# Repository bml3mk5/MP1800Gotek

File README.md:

# ディスクインターフェース for MP-1800 / MP-1805 on 日立ベーシックマスターレベル３

## フォルダ構成

    Board/ ......................... 基板設計(KiCAD Version 6)

-----
# Disk Interface for MP-1800 / MP-1805 on HITACH BASIC MASTER LEVEL3

## Folders:

    Board/ ......................... Circuit board design(KiCAD Version 6)

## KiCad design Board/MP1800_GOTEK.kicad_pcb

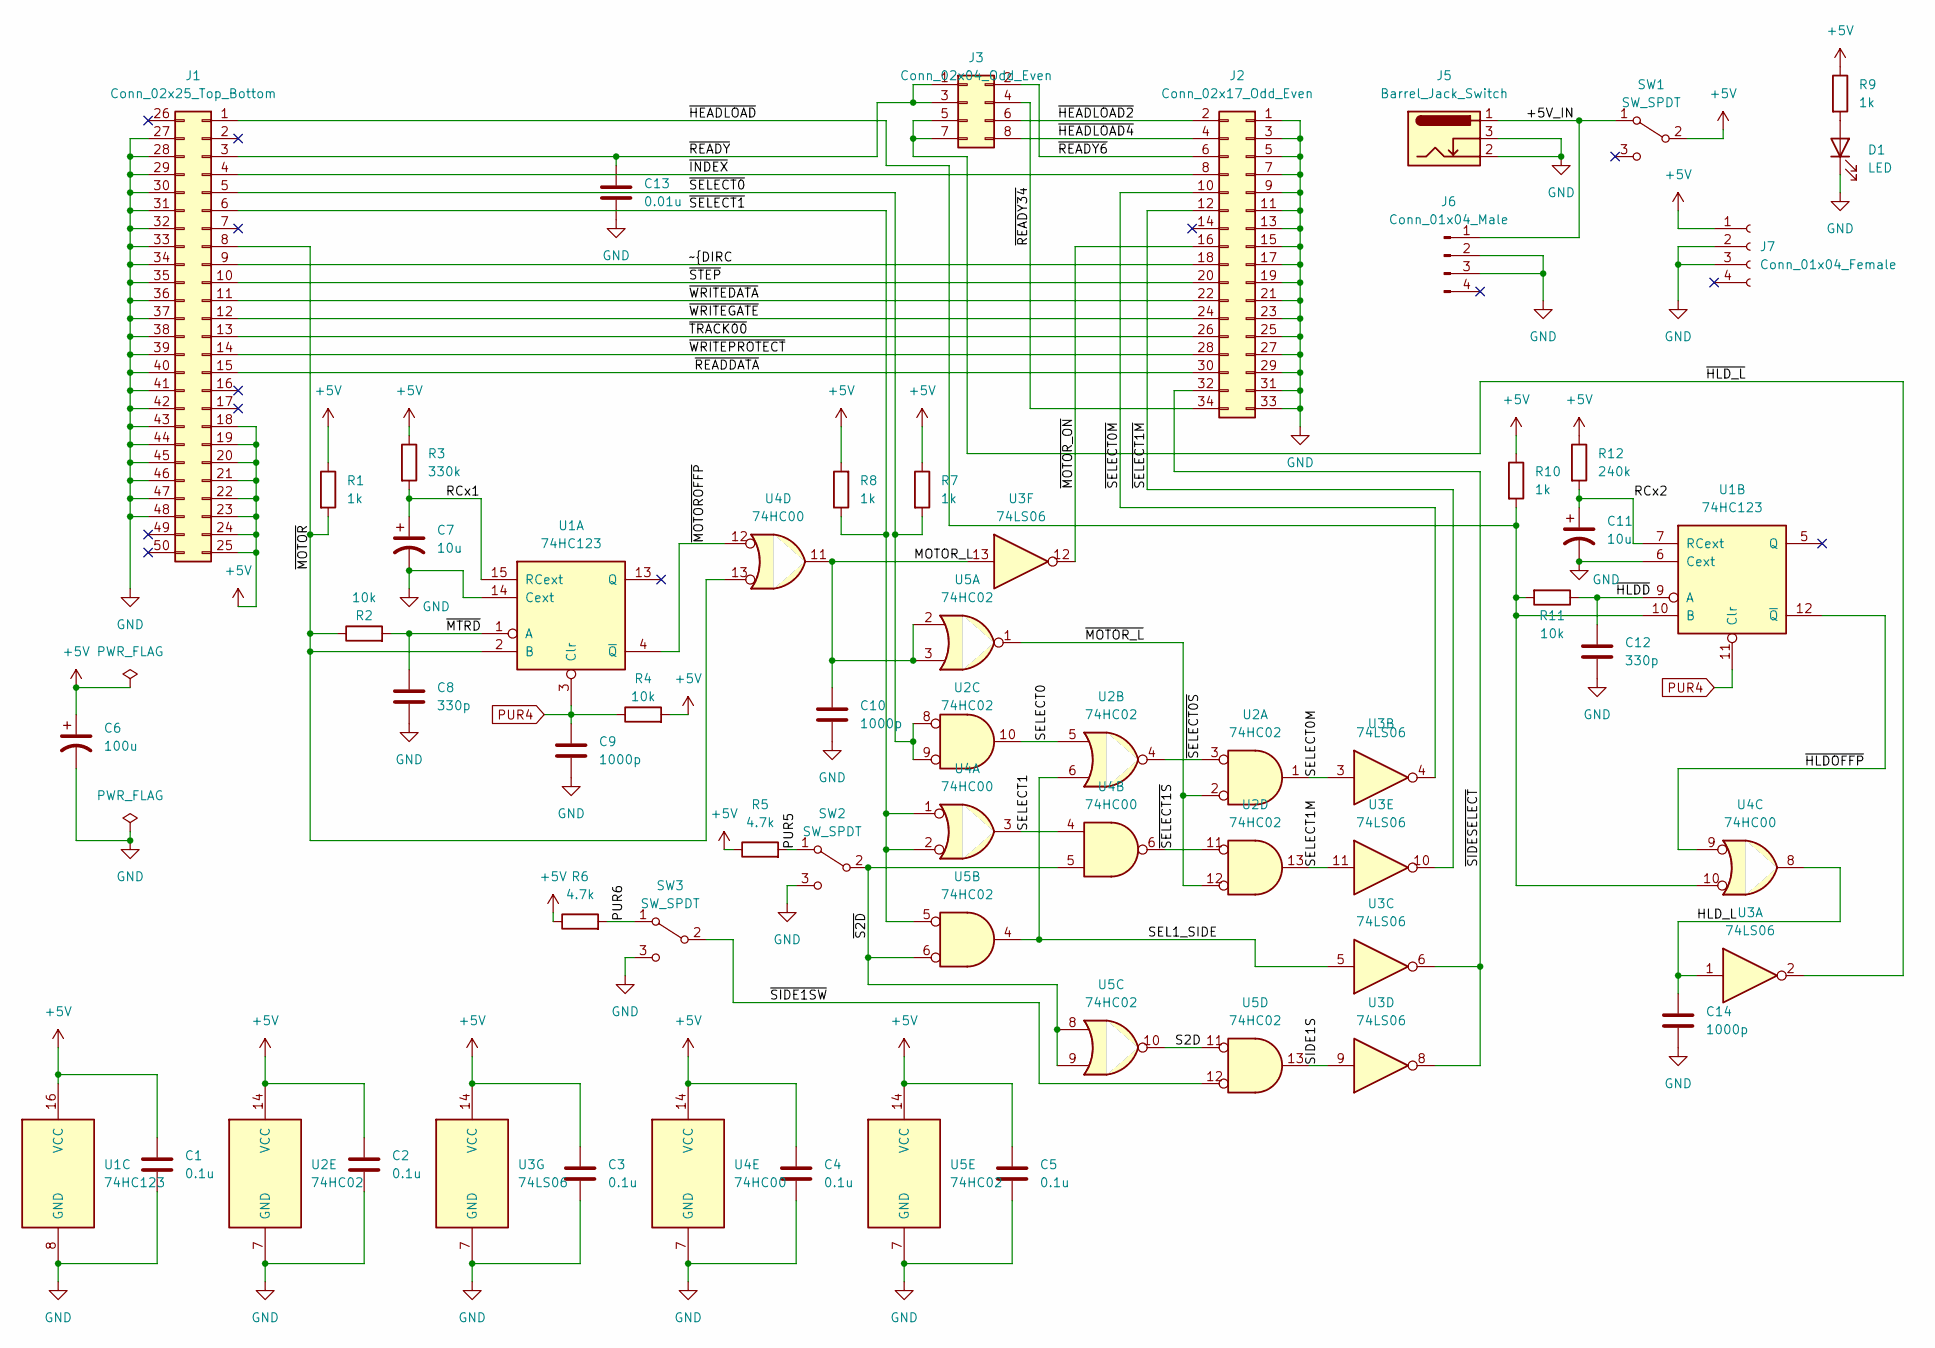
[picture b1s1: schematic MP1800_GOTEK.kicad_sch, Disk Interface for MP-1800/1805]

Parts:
C1, C2, C3, C4, C5: 0.1u; C_Disc_D3.0mm_W2.0mm_P2.50mm
C6: 100u; CP_Radial_D6.3mm_P2.50mm
C7, C11: 10u; CP_Radial_D6.3mm_P2.50mm
C8, C12: 330p; C_Disc_D3.0mm_W2.0mm_P2.50mm
C9, C10, C14: 1000p; C_Disc_D3.0mm_W2.0mm_P2.50mm
C13: 0.01u; C_Disc_D3.0mm_W2.0mm_P2.50mm
D1: LED; LED_D3.0mm
J1: Conn_02x25_Top_Bottom; YA_PinHeader_2x25_P2.54mm_Vertical
J2: Conn_02x17_Odd_Even; YA_PinHeader_2x17_P2.54mm_Vertical
J3: Conn_02x04_Odd_Even; PinHeader_2x04_P2.54mm_Vertical
J5: Barrel_Jack_Switch; YA_BarrelJack_CUI_PJ-102AH_Horizontal
J6: Conn_01x04_Male; PinHeader_1x04_P2.54mm_Horizontal
J7: Conn_01x04_Female; PinSocket_1x04_P2.54mm_Vertical
R1, R7, R8, R9, R10: 1k; R_Axial_DIN0207_L6.3mm_D2.5mm_P2.54mm_Vertical
R2, R4, R11: 10k; R_Axial_DIN0207_L6.3mm_D2.5mm_P2.54mm_Vertical
R3: 330k; R_Axial_DIN0207_L6.3mm_D2.5mm_P2.54mm_Vertical
R5, R6: 4.7k; R_Axial_DIN0207_L6.3mm_D2.5mm_P2.54mm_Vertical
R12: 240k; R_Axial_DIN0207_L6.3mm_D2.5mm_P2.54mm_Vertical
SW1: SW_SPDT; SW_Switch_SS12D10_SPDT
SW2, SW3: SW_SPDT; SW_Switch_SS12D00_SPDT
U1: 74HC123; DIP-16_W7.62mm_Socket
U2, U5: 74HC02; DIP-14_W7.62mm_Socket
U3: 74LS06; DIP-14_W7.62mm_Socket
U4: 74HC00; DIP-14_W7.62mm_Socket

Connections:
+5V: C1.2, C2.2, C3.2, C4.2, C5.2, C6.1, J1.18, J1.19, J1.20, J1.21, J1.22, J1.23, J1.24, J1.25, J7.1, R1.1, R3.1, R4.2, R5.1, R6.1, R7.1, R8.2, R9.1, R10.1, R12.1, SW1.2 (B), U1.16 (VCC), U2.14 (VCC), U3.14 (VCC), U4.14 (VCC), U5.14 (VCC)
/+5V_IN: J5.1, J6.1, SW1.1 (A)
/HLD_L: C14.2, U3.1, U4.8
/MOTOR_L: C10.2, U3.13, U4.11, U5.2, U5.3
/PUR5: R5.2, SW2.1 (A)
/PUR6: R6.2, SW3.1 (A)
/RCx1: C7.1, R3.2, U1.15 (RCext)
/RCx2: C11.1, R12.2, U1.7 (RCext)
/S2D: U5.10, U5.11
/SEL1_SIDE: U2.6, U3.5, U5.4
/SELECT0: U2.5, U2.10
/SELECT0M: U2.1, U3.3
/SELECT1: U4.3, U4.4
/SELECT1M: U2.13, U3.11
/SIDE1S: U3.9, U5.13
/~DIRC: J1.9, J2.18
/~HEADLOAD2: J2.2, J3.6
/~HEADLOAD4: J2.4, J3.8
/~HEADLOAD: J1.1, R10.2, R11.2, U1.10 (B), U4.10
/~HLDD: C12.2, R11.1, U1.9 (A)
/~HLDOFFP: U1.12 (~Q), U4.9
/~HLD_L: J3.5, J3.7, U3.2
/~INDEX: J1.4, J2.8
/~MOTOROFFP: U1.4 (~Q), U4.12
/~MOTOR_L: U2.2, U2.12, U5.1
/~MOTOR_ON: J2.16, U3.12
/~MOTOR: J1.8, R1.2, R2.1, U1.2 (B), U4.13
/~MTRD: C8.2, R2.2, U1.1 (A)
/~READDATA: J1.15, J2.30
/~READY6: J2.6, J3.2
/~READY34: J2.34, J3.4
/~READY: C13.2, J1.3, J3.1, J3.3
/~S2D: SW2.2 (B), U4.5, U5.6, U5.8, U5.9
/~SELECT0M: J2.10, U3.4
/~SELECT0S: U2.3, U2.4
/~SELECT0: J1.5, R7.2, U2.8, U2.9
/~SELECT1M: J2.12, U3.10
/~SELECT1S: U2.11, U4.6
/~SELECT1: J1.6, R8.1, U4.1, U4.2, U5.5
/~SIDE1SW: SW3.2 (B), U5.12
/~SIDESELECT: J2.32, U3.6, U3.8
/~STEP: J1.10, J2.20
/~TRACK00: J1.13, J2.26
/~WRITEDATA: J1.11, J2.22
/~WRITEGATE: J1.12, J2.24
/~WRITEPROTECT: J1.14, J2.28
GND: C1.1, C2.1, C3.1, C4.1, C5.1, C6.2, C7.2, C8.1, C9.1, C10.1, C11.2, C12.1, C13.1, C14.1, D1.1 (K), J1.27, J1.28, J1.29, J1.30, J1.31, J1.32, J1.33, J1.34, J1.35, J1.36, J1.37, J1.38, J1.39, J1.40, J1.41, J1.42, J1.43, J1.44, J1.45, J1.46, J1.47, J1.48, J2.1, J2.3, J2.5, J2.7, J2.9, J2.11, J2.13, J2.15, J2.17, J2.19, J2.21, J2.23, J2.25, J2.27, J2.29, J2.31, J2.33, J5.2, J5.3, J6.2, J6.3, J7.2, J7.3, SW2.3 (C), SW3.3 (C), U1.6 (Cext), U1.8 (GND), U1.14 (Cext), U2.7 (GND), U3.7 (GND), U4.7 (GND), U5.7 (GND)
unnamed: D1.2 (A), R9.2
PUR4: C9.2, R4.1, U1.3 (Clr), U1.11 (Clr)

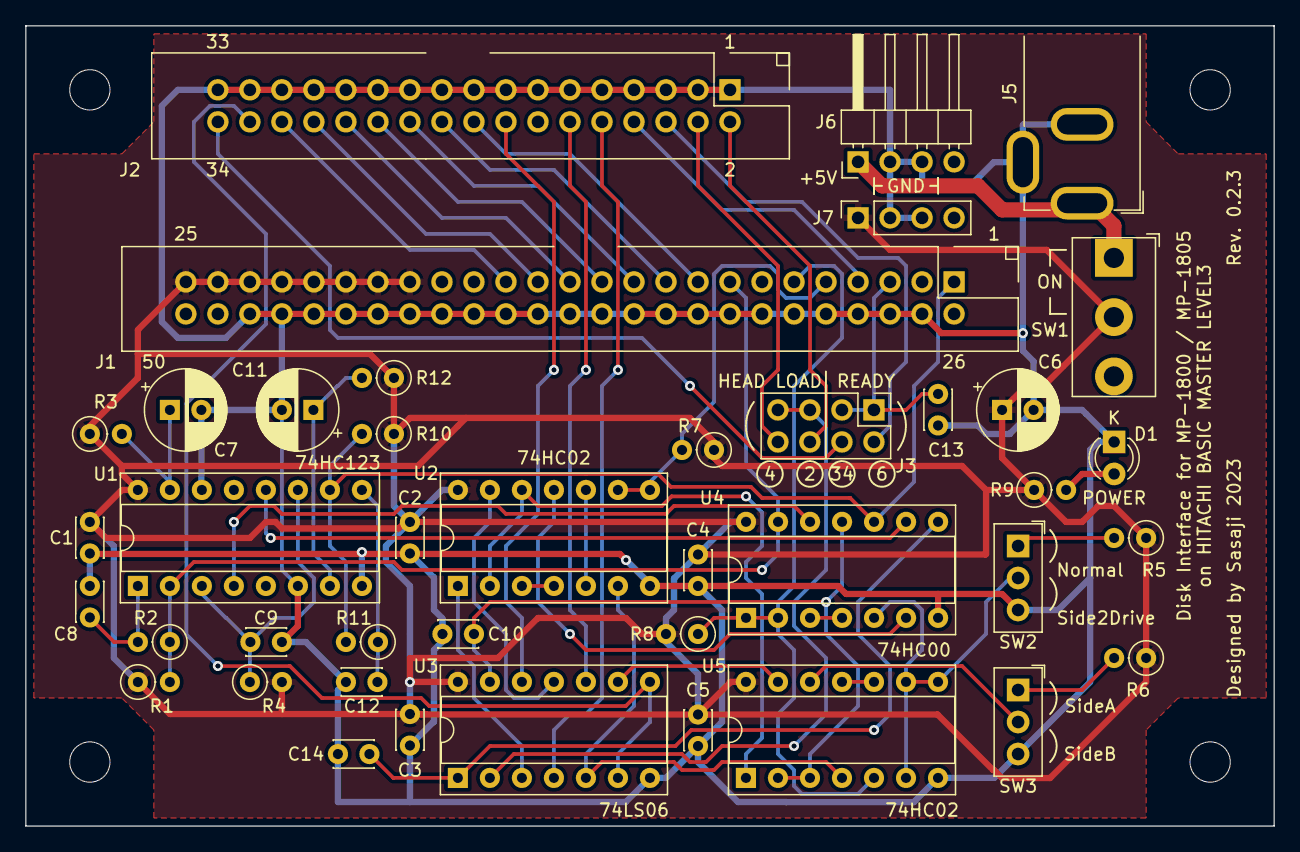
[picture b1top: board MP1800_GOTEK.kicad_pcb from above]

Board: 2 copper layers, 99.1 x 63.5 mm, 41 parts (0 on the bottom side), 49 nets.

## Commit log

2023-11-18 Version 0.2.2
2023-11-18 Revision 0.2.3
